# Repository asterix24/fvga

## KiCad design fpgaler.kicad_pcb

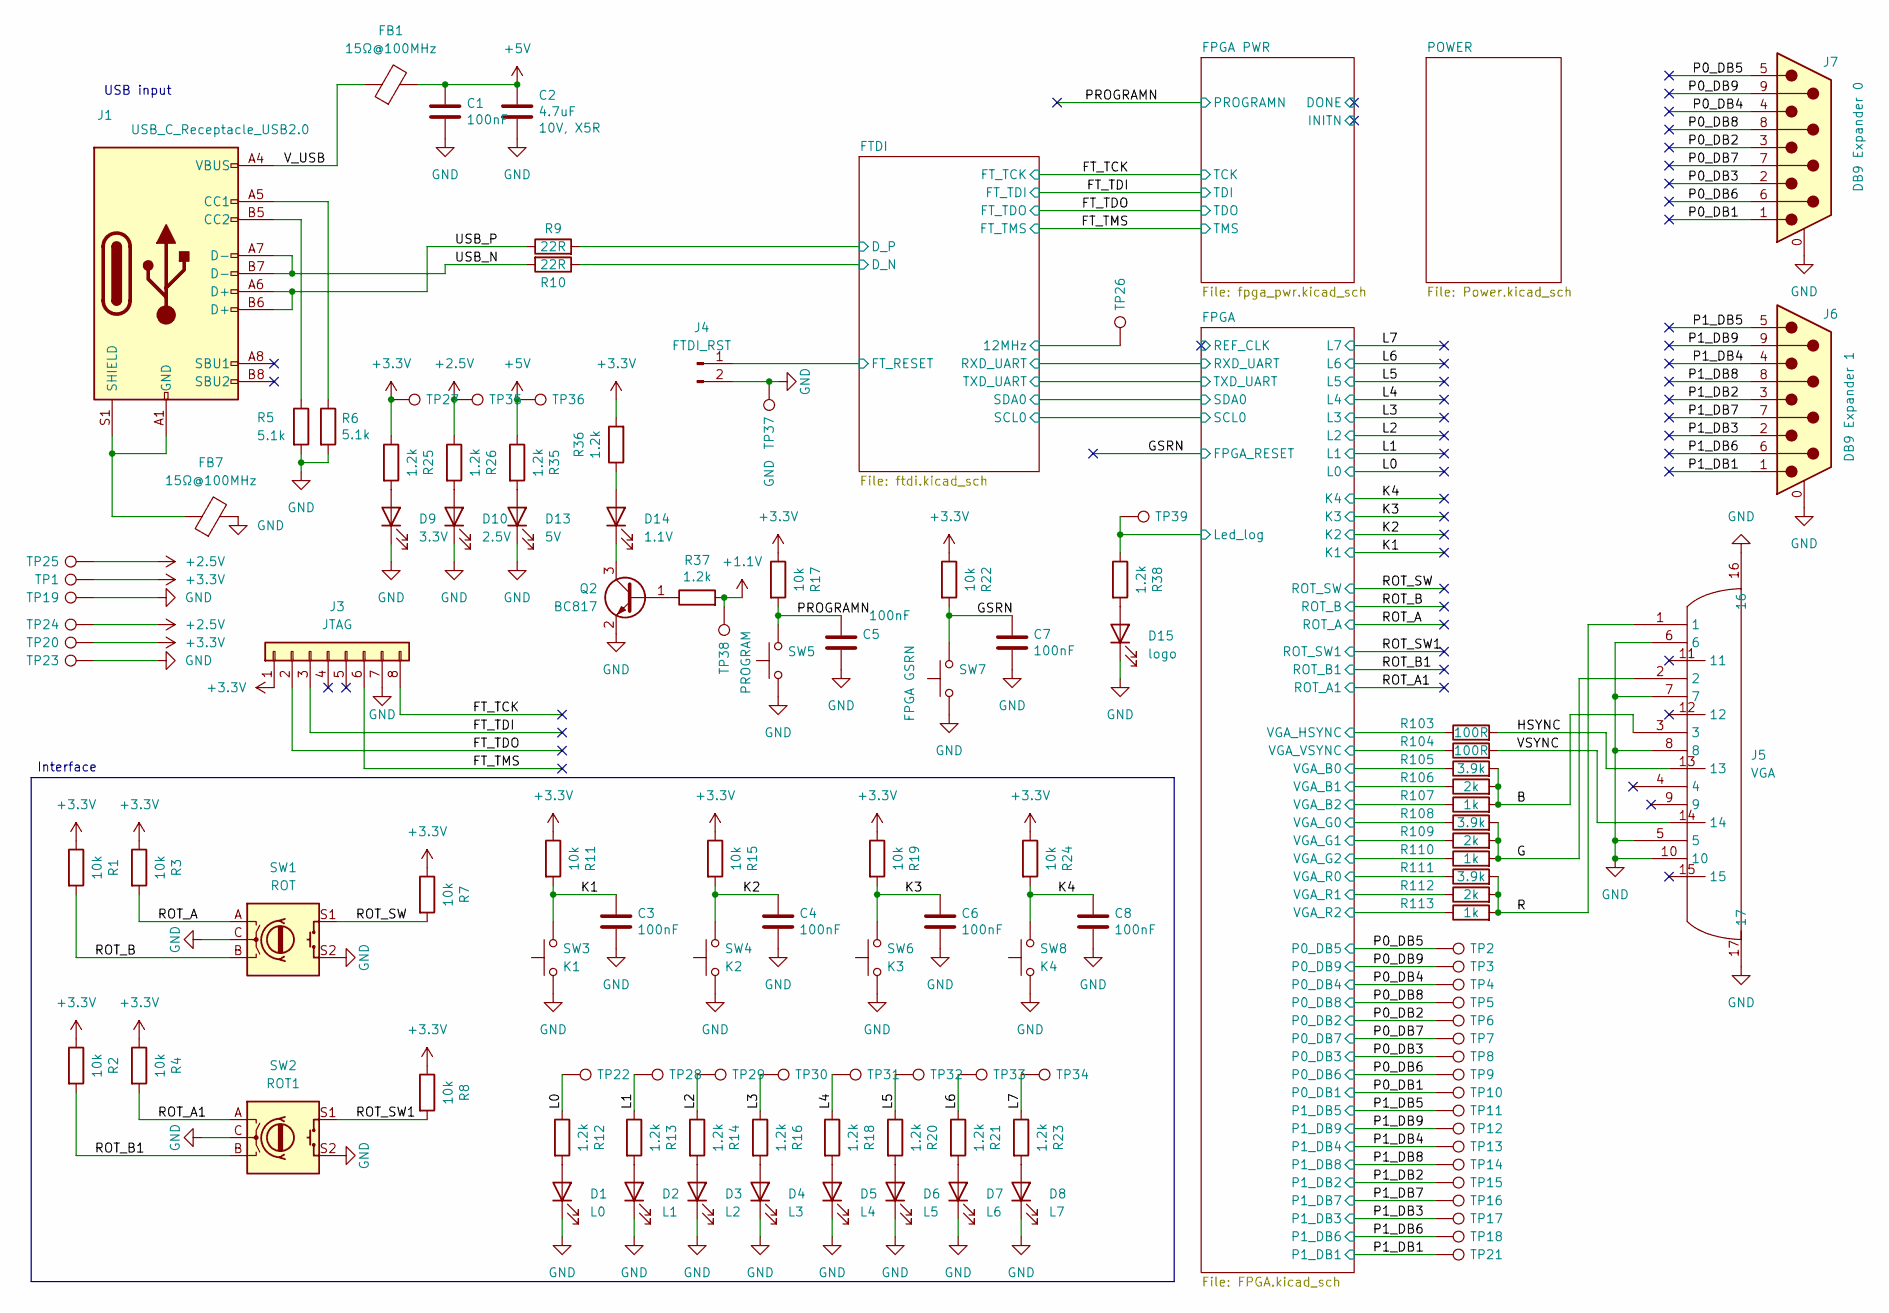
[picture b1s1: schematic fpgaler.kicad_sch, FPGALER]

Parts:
C1, C3, C4, C5, C6, C7, C8: 100nF; C_0603_1608Metric
C2: 4.7uF; C_0805_2012Metric
D1: L0; D_0603_1608Metric
D2: L1; D_0603_1608Metric
D3: L2; D_0603_1608Metric
D4: L3; D_0603_1608Metric
D5: L4; D_0603_1608Metric
D6: L5; D_0603_1608Metric
D7: L6; D_0603_1608Metric
D8: L7; D_0603_1608Metric
D9: 3.3V; D_0603_1608Metric
D10: 2.5V; D_0603_1608Metric
D13: 5V; D_0603_1608Metric
D14: 1.1V; D_0603_1608Metric
D15: logo; D_0603_1608Metric
FB1, FB7: 15Ω@100MHz; L_0603_1608Metric_Pad1.05x0.95mm_HandSolder
J1: USB_C_Receptacle_USB2.0; USB_C_Receptacle_HRO_TYPE-C-31-M-12
J3: JTAG; PinHeader_1x08_P2.54mm_Vertical
J4: FTDI_RST; PinHeader_1x02_P2.54mm_Vertical
J5: VGA; DSUB-TH_HYC06-HDR15B-060; Manufacturer Part HYC06-HDR15B-060; LCSC Part Name 高密度D-Sub 母 P数:15P
J6: DB9 Expander 1; DSUB-9_Pins_Horizontal_P2.77x2.84mm_EdgePinOffset4.94mm_Hou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
J7: DB9 Expander 0; DSUB-9_Pins_Horizontal_P2.77x2.84mm_EdgePinOffset4.94mm_Hou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
Q2: BC817; SOT-23
R1, R2, R3, R4, R7, R8, R11, R15, R17, R19, R22, R24: 10k; R_0603_1608Metric
R5, R6: 5.1k; R_0603_1608Metric
R9, R10: 22R; R_0402_1005Metric_Pad0.72x0.64mm_HandSolder
R12, R13, R14, R16, R18, R20, R21, R23, R25, R26, R35, R36, R37, R38: 1.2k; R_0603_1608Metric
R103, R104: 100R; R_0603_1608Metric
R105, R108, R111: 3.9k; R_0603_1608Metric
R106, R109, R112: 2k; R_0603_1608Metric
R107, R110, R113: 1k; R_0603_1608Metric
SW1: ROT; RotaryEncoder_Alps_EC11E-Switch_Vertical_H20mm_CircularMoun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
SW2: ROT1; RotaryEncoder_Alps_EC11E-Switch_Vertical_H20mm_CircularMoun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
SW3: K1; SW_PUSH_1P1T_6x3.5mm_H4.3_APEM_MJTP1243
SW4: K2; SW_PUSH_1P1T_6x3.5mm_H4.3_APEM_MJTP1243
SW5: PROGRAM; SW_PUSH_1P1T_6x3.5mm_H4.3_APEM_MJTP1243
SW6: K3; SW_PUSH_1P1T_6x3.5mm_H4.3_APEM_MJTP1243
SW7: FPGA GSRN; SW_PUSH_1P1T_6x3.5mm_H4.3_APEM_MJTP1243
SW8: K4; SW_PUSH_1P1T_6x3.5mm_H4.3_APEM_MJTP1243
TP1, TP2, TP3, TP4, TP5, TP6, TP7, TP8, TP9, TP10, TP11, TP12, TP13, TP14, TP15, TP16, TP17, TP18, TP19, TP20, TP21, TP22, TP23, TP24, TP25, TP26, TP28, TP29, TP30, TP31, TP32, TP33, TP34, TP39: TestPoint; TestPoint_THTPad_D1.5mm_Drill0.7mm
TP27: 3.3V; TestPoint_THTPad_D1.5mm_Drill0.7mm
TP35: 2.5V; TestPoint_THTPad_D1.5mm_Drill0.7mm
TP36, TP38: 5V; TestPoint_THTPad_D1.5mm_Drill0.7mm
TP37: GND; TestPoint_THTPad_D1.5mm_Drill0.7mm

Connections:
+1.1V: R37.2, TP38.1; also elsewhere on the board
+2.5V: R26.1, TP24.1, TP25.1, TP35.1; also elsewhere on the board
+3.3V: J3.1, R1.1, R2.1, R3.1, R4.1, R7.1, R8.1, R11.1, R15.1, R17.1, R19.1, R22.1, R24.1, R25.1, R36.2, TP1.1, TP20.1, TP27.1; also elsewhere on the board
+5V: C1.1, C2.1, FB1.2, R35.1, TP36.1; also elsewhere on the board
/B: J5.3, R105.2, R106.2, R107.2
/FPGA/Led_log: R38.1, TP39.1; also elsewhere on the board
/FPGA/VGA_B0: R105.1; also elsewhere on the board
/FPGA/VGA_B1: R106.1; also elsewhere on the board
/FPGA/VGA_B2: R107.1; also elsewhere on the board
/FPGA/VGA_G0: R108.1; also elsewhere on the board
/FPGA/VGA_G1: R109.1; also elsewhere on the board
/FPGA/VGA_G2: R110.1; also elsewhere on the board
/FPGA/VGA_HSYNC: R103.1; also elsewhere on the board
/FPGA/VGA_R0: R111.1; also elsewhere on the board
/FPGA/VGA_R1: R112.1; also elsewhere on the board
/FPGA/VGA_R2: R113.1; also elsewhere on the board
/FPGA/VGA_VSYNC: R104.1; also elsewhere on the board
/FTDI/12MHz: TP26.1; also elsewhere on the board
/FTDI/D_N: R10.1; also elsewhere on the board
/FTDI/D_P: R9.2; also elsewhere on the board
/FTDI/FT_RESET: J4.1; also elsewhere on the board
/FT_TCK: J3.8; also elsewhere on the board
/FT_TDI: J3.3; also elsewhere on the board
/FT_TDO: J3.2; also elsewhere on the board
/FT_TMS: J3.6; also elsewhere on the board
/G: J5.2, R108.2, R109.2, R110.2
/GSRN: C7.2, R22.2, SW7.2; also elsewhere on the board
/HSYNC: J5.13, R103.2
/K1: C3.2, R11.2, SW3.2; also elsewhere on the board
/K2: C4.2, R15.2, SW4.2; also elsewhere on the board
/K3: C6.2, R19.2, SW6.2; also elsewhere on the board
/K4: C8.2, R24.2, SW8.2; also elsewhere on the board
/L0: R12.1, TP22.1; also elsewhere on the board
/L1: R13.1, TP28.1; also elsewhere on the board
/L2: R14.1, TP29.1; also elsewhere on the board
/L3: R16.1, TP30.1; also elsewhere on the board
/L4: R18.1, TP31.1; also elsewhere on the board
/L5: R20.1, TP32.1; also elsewhere on the board
/L6: R21.1, TP33.1; also elsewhere on the board
/L7: R23.1, TP34.1; also elsewhere on the board
/P0_DB1: J7.1, TP10.1; also elsewhere on the board
/P0_DB2: J7.3, TP6.1; also elsewhere on the board
/P0_DB3: J7.2, TP8.1; also elsewhere on the board
/P0_DB4: J7.4, TP4.1; also elsewhere on the board
/P0_DB5: J7.5, TP2.1; also elsewhere on the board
/P0_DB6: J7.6, TP9.1; also elsewhere on the board
/P0_DB7: J7.7, TP7.1; also elsewhere on the board
/P0_DB8: J7.8, TP5.1; also elsewhere on the board
/P0_DB9: J7.9, TP3.1; also elsewhere on the board
/P1_DB1: J6.1, TP21.1; also elsewhere on the board
/P1_DB2: J6.3, TP15.1; also elsewhere on the board
/P1_DB3: J6.2, TP17.1; also elsewhere on the board
/P1_DB4: J6.4, TP13.1; also elsewhere on the board
/P1_DB5: J6.5, TP11.1; also elsewhere on the board
/P1_DB6: J6.6, TP18.1; also elsewhere on the board
/P1_DB7: J6.7, TP16.1; also elsewhere on the board
/P1_DB8: J6.8, TP14.1; also elsewhere on the board
/P1_DB9: J6.9, TP12.1; also elsewhere on the board
/PROGRAMN: C5.2, R17.2, SW5.2; also elsewhere on the board
/R: J5.1, R111.2, R112.2, R113.2
/ROT_A: R3.2, SW1.A; also elsewhere on the board
/ROT_A1: R4.2, SW2.A; also elsewhere on the board
/ROT_B: R1.2, SW1.B; also elsewhere on the board
/ROT_B1: R2.2, SW2.B; also elsewhere on the board
/ROT_SW: R7.2, SW1.S1; also elsewhere on the board
/ROT_SW1: R8.2, SW2.S1; also elsewhere on the board
/USB_N: J1.A7 (D-), J1.B7 (D-), R10.2
/USB_P: J1.A6 (D+), J1.B6 (D+), R9.1
/VSYNC: J5.14, R104.2
/V_USB: FB1.1, J1.A4 (VBUS), J1.A9 (VBUS), J1.B4 (VBUS), J1.B9 (VBUS)
GND: C1.2, C2.2, C3.1, C4.1, C5.1, C6.1, C7.1, C8.1, D1.1 (K), D2.1 (K), D3.1 (K), D4.1 (K), D5.1 (K), D6.1 (K), D7.1 (K), D8.1 (K), D9.1 (K), D10.1 (K), D13.1 (K), D15.1 (K), FB7.2, J3.7, J4.2, J5.5, J5.6, J5.7, J5.8, J5.10, J5.16, J5.17, J6.0 (PAD), J7.0 (PAD), Q2.2 (E), R5.2, R6.2, SW1.C, SW1.S2, SW2.C, SW2.S2, SW3.1, SW4.1, SW5.1, SW6.1, SW7.1, SW8.1, TP19.1, TP23.1, TP37.1; also elsewhere on the board
unnamed: D1.2 (A), R12.2
unnamed: D2.2 (A), R13.2
unnamed: D3.2 (A), R14.2
unnamed: D4.2 (A), R16.2
unnamed: D5.2 (A), R18.2
unnamed: D6.2 (A), R20.2
unnamed: D7.2 (A), R21.2
unnamed: D8.2 (A), R23.2
unnamed: D9.2 (A), R25.2
unnamed: D10.2 (A), R26.2
unnamed: D13.2 (A), R35.2
unnamed: D14.2 (A), R36.1
unnamed: D14.1 (K), Q2.3 (C)
unnamed: D15.2 (A), R38.2
unnamed: J1.A5 (CC1), R6.1
unnamed: J1.B5 (CC2), R5.1
unnamed: FB7.1, J1.A1 (GND), J1.A12 (GND), J1.B1 (GND), J1.B12 (GND), J1.S1 (SHIELD)
unnamed: Q2.1 (B), R37.1

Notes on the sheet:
Interface
USB input

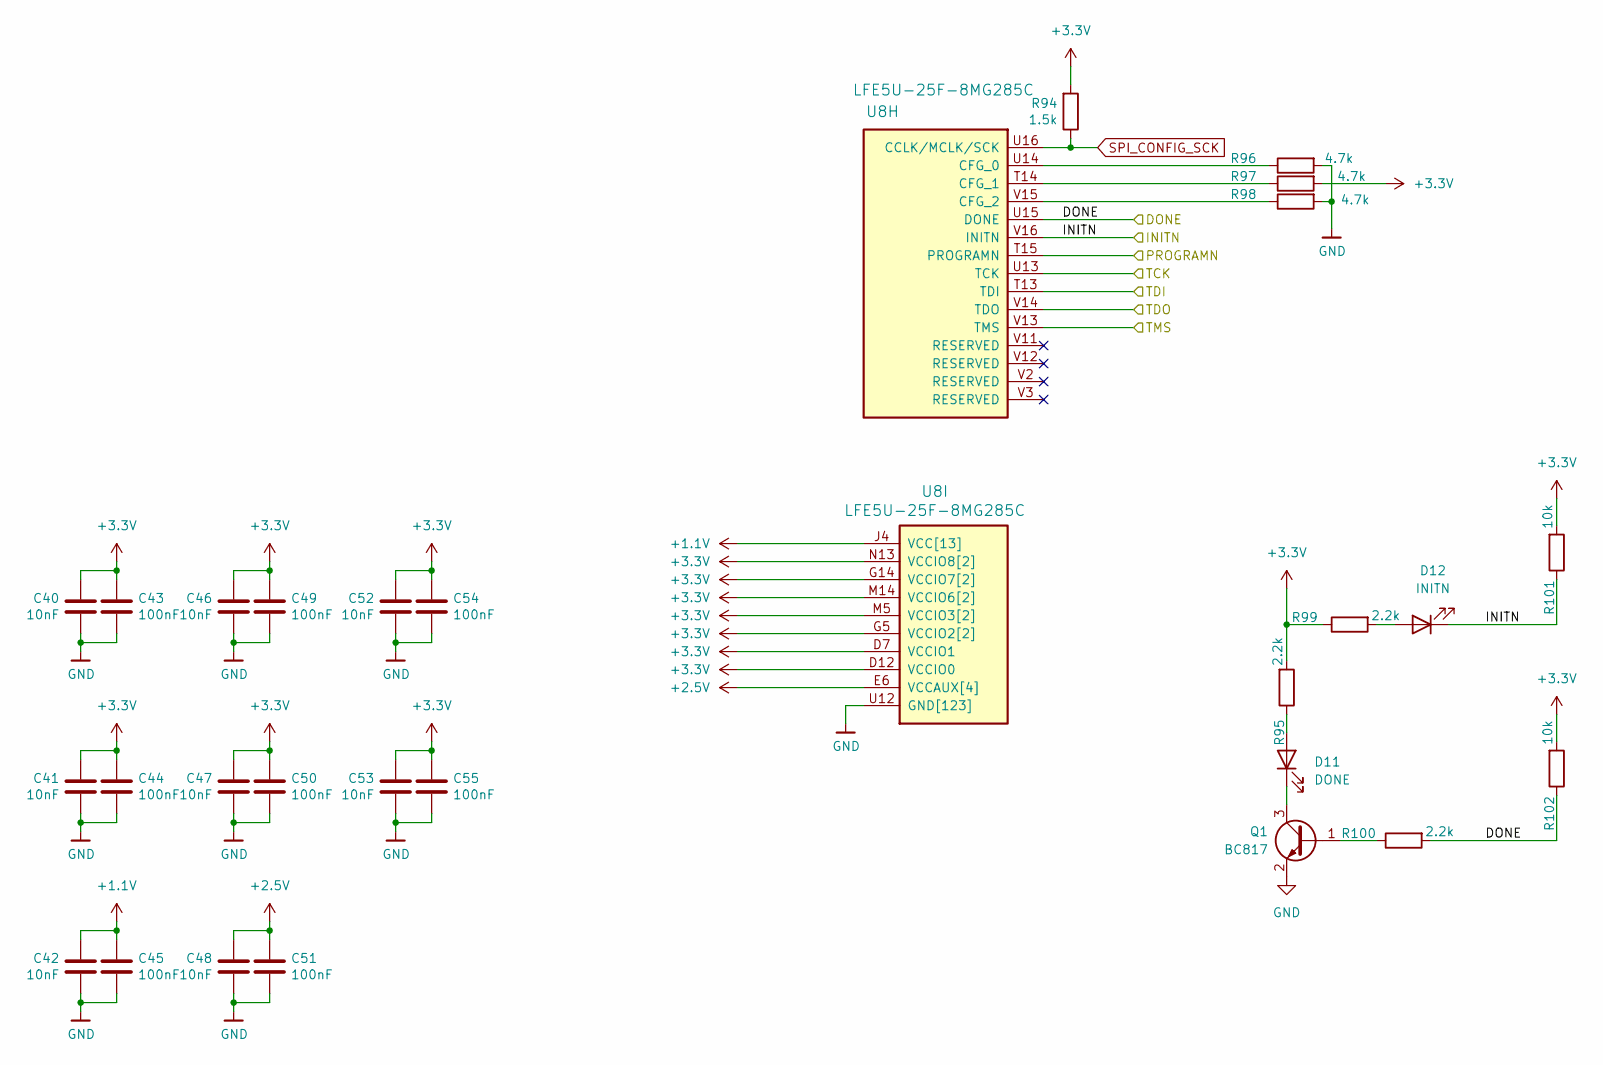
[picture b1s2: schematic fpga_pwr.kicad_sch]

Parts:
C40, C41, C42, C46, C47, C48, C52, C53: 10nF; C_0603_1608Metric
C43, C44, C45, C49, C50, C51, C54, C55: 100nF; C_0603_1608Metric
D11: DONE; D_0603_1608Metric
D12: INITN; D_0603_1608Metric
Q1: BC817; SOT-23
R94: 1.5k; R_0603_1608Metric; LCSC C22843
R95, R99: 2.2k; R_0603_1608Metric
R96, R97, R98: 4.7k; R_0603_1608Metric
R100: 2.2k; R_0603_1608Metric; LCSC C4190
R101, R102: 10k; R_0603_1608Metric
U8: LFE5U-25F-8MG285C; BGA-285; LCSC C5664013

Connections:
+1.1V: C42.1, C45.1, U8.D8 (VCC[13]), U8.D9 (VCC[13]), U8.D10 (VCC[13]), U8.D11 (VCC[13]), U8.J4 (VCC[13]), U8.J5 (VCC[13]), U8.J14 (VCC[13]), U8.J15 (VCC[13]), U8.M4 (VCC[13]), U8.M15 (VCC[13]), U8.P7 (VCC[13]), U8.P9 (VCC[13]), U8.P11 (VCC[13]); also elsewhere on the board
+2.5V: C48.1, C51.1, U8.E6 (VCCAUX[4]), U8.E13 (VCCAUX[4]), U8.N6 (VCCAUX[4]), U8.P13 (VCCAUX[4]); also elsewhere on the board
+3.3V: C40.1, C41.1, C43.1, C44.1, C46.1, C47.1, C49.1, C50.1, C52.1, C53.1, C54.1, C55.1, R94.2, R95.2, R97.2, R99.1, R101.2, R102.2, U8.D7 (VCCIO1), U8.D12 (VCCIO0), U8.G5 (VCCIO2[2]), U8.G14 (VCCIO7[2]), U8.H5 (VCCIO2[2]), U8.H14 (VCCIO7[2]), U8.M5 (VCCIO3[2]), U8.M14 (VCCIO6[2]), U8.N5 (VCCIO3[2]), U8.N13 (VCCIO8[2]), U8.N14 (VCCIO6[2]), U8.P14 (VCCIO8[2]); also elsewhere on the board
/FPGA PWR/DONE: R100.2, R102.1, U8.U15 (DONE)
/FPGA PWR/INITN: D12.1 (K), R101.1, U8.V16 (INITN)
/FT_TCK: U8.U13 (TCK); also elsewhere on the board
/FT_TDI: U8.T13 (TDI); also elsewhere on the board
/FT_TDO: U8.V14 (TDO); also elsewhere on the board
/FT_TMS: U8.V13 (TMS); also elsewhere on the board
/PROGRAMN: U8.T15 (PROGRAMN); also elsewhere on the board
GND: C40.2, C41.2, C42.2, C43.2, C44.2, C45.2, C46.2, C47.2, C48.2, C49.2, C50.2, C51.2, C52.2, C53.2, C54.2, C55.2, Q1.2 (E), R96.2, R98.2, U8.B3 (GND[123]), U8.B16 (GND[123]), U8.E5 (GND[123]), U8.E7 (GND[123]), U8.E8 (GND[123]), U8.E9 (GND[123]), U8.E10 (GND[123]), U8.E11 (GND[123]), U8.E12 (GND[123]), U8.E14 (GND[123]), U8.F5 (GND[123]), U8.F6 (GND[123]), U8.F7 (GND[123]), U8.F8 (GND[123]), U8.F9 (GND[123]), U8.F10 (GND[123]), U8.F11 (GND[123]), U8.F12 (GND[123]), U8.F13 (GND[123]), U8.F14 (GND[123]), U8.G2 (GND[123]), U8.G6 (GND[123]), U8.G7 (GND[123]), U8.G8 (GND[123]), U8.G9 (GND[123]), U8.G10 (GND[123]), U8.G11 (GND[123]), U8.G12 (GND[123]), U8.G13 (GND[123]), U8.G17 (GND[123]), U8.H6 (GND[123]), U8.H7 (GND[123]), U8.H8 (GND[123]), U8.H9 (GND[123]), U8.H10 (GND[123]), U8.H11 (GND[123]), U8.H12 (GND[123]), U8.H13 (GND[123]), U8.J6 (GND[123]), U8.J7 (GND[123]), U8.J8 (GND[123]), U8.J9 (GND[123]), U8.J10 (GND[123]), U8.J11 (GND[123]), U8.J12 (GND[123]), U8.J13 (GND[123]), U8.K5 (GND[123]), U8.K6 (GND[123]), U8.K7 (GND[123]), U8.K8 (GND[123]), U8.K9 (GND[123]), U8.K10 (GND[123]), U8.K11 (GND[123]), U8.K12 (GND[123]), U8.K13 (GND[123]), U8.K14 (GND[123]), U8.L2 (GND[123]), U8.L5 (GND[123]), U8.L6 (GND[123]), U8.L7 (GND[123]), U8.L8 (GND[123]), U8.L9 (GND[123]), U8.L10 (GND[123]), U8.L11 (GND[123]), U8.L12 (GND[123]), U8.L13 (GND[123]), U8.L14 (GND[123]), U8.L17 (GND[123]), U8.M6 (GND[123]), U8.M7 (GND[123]), U8.M8 (GND[123]), U8.M9 (GND[123]), U8.M10 (GND[123]), U8.M11 (GND[123]), U8.M12 (GND[123]), U8.M13 (GND[123]), U8.N7 (GND[123]), U8.N8 (GND[123]), U8.N9 (GND[123]), U8.N10 (GND[123]), U8.N11 (GND[123]), U8.N12 (GND[123]), U8.P5 (GND[123]), U8.P6 (GND[123]), U8.P8 (GND[123]), U8.P10 (GND[123]), U8.P12 (GND[123]), U8.R1 (GND[123]), U8.R2 (GND[123]), U8.R3 (GND[123]), U8.R10 (GND[123]), U8.T1 (GND[123]), U8.T2 (GND[123]), U8.T3 (GND[123]), U8.T4 (GND[123]), U8.T5 (GND[123]), U8.T6 (GND[123]), U8.T7 (GND[123]), U8.T8 (GND[123]), U8.T9 (GND[123]), U8.T10 (GND[123]), U8.T11 (GND[123]), U8.T12 (GND[123]), U8.T16 (GND[123]), U8.U1 (GND[123]), U8.U2 (GND[123]), U8.U3 (GND[123]), U8.U4 (GND[123]), U8.U5 (GND[123]), U8.U6 (GND[123]), U8.U7 (GND[123]), U8.U8 (GND[123]), U8.U9 (GND[123]), U8.U10 (GND[123]), U8.U11 (GND[123]), U8.U12 (GND[123]), U8.V4 (GND[123]), U8.V5 (GND[123]), U8.V6 (GND[123]), U8.V7 (GND[123]), U8.V8 (GND[123]), U8.V9 (GND[123]), U8.V10 (GND[123]); also elsewhere on the board
unnamed: D11.2 (A), R95.1
unnamed: D11.1 (K), Q1.3 (C)
unnamed: D12.2 (A), R99.2
unnamed: Q1.1 (B), R100.1
unnamed: R96.1, U8.U14 (CFG_0)
unnamed: R97.1, U8.T14 (CFG_1)
unnamed: R98.1, U8.V15 (CFG_2)
SPI_CONFIG_SCK: R94.1, U8.U16 (CCLK/MCLK/SCK); also elsewhere on the board

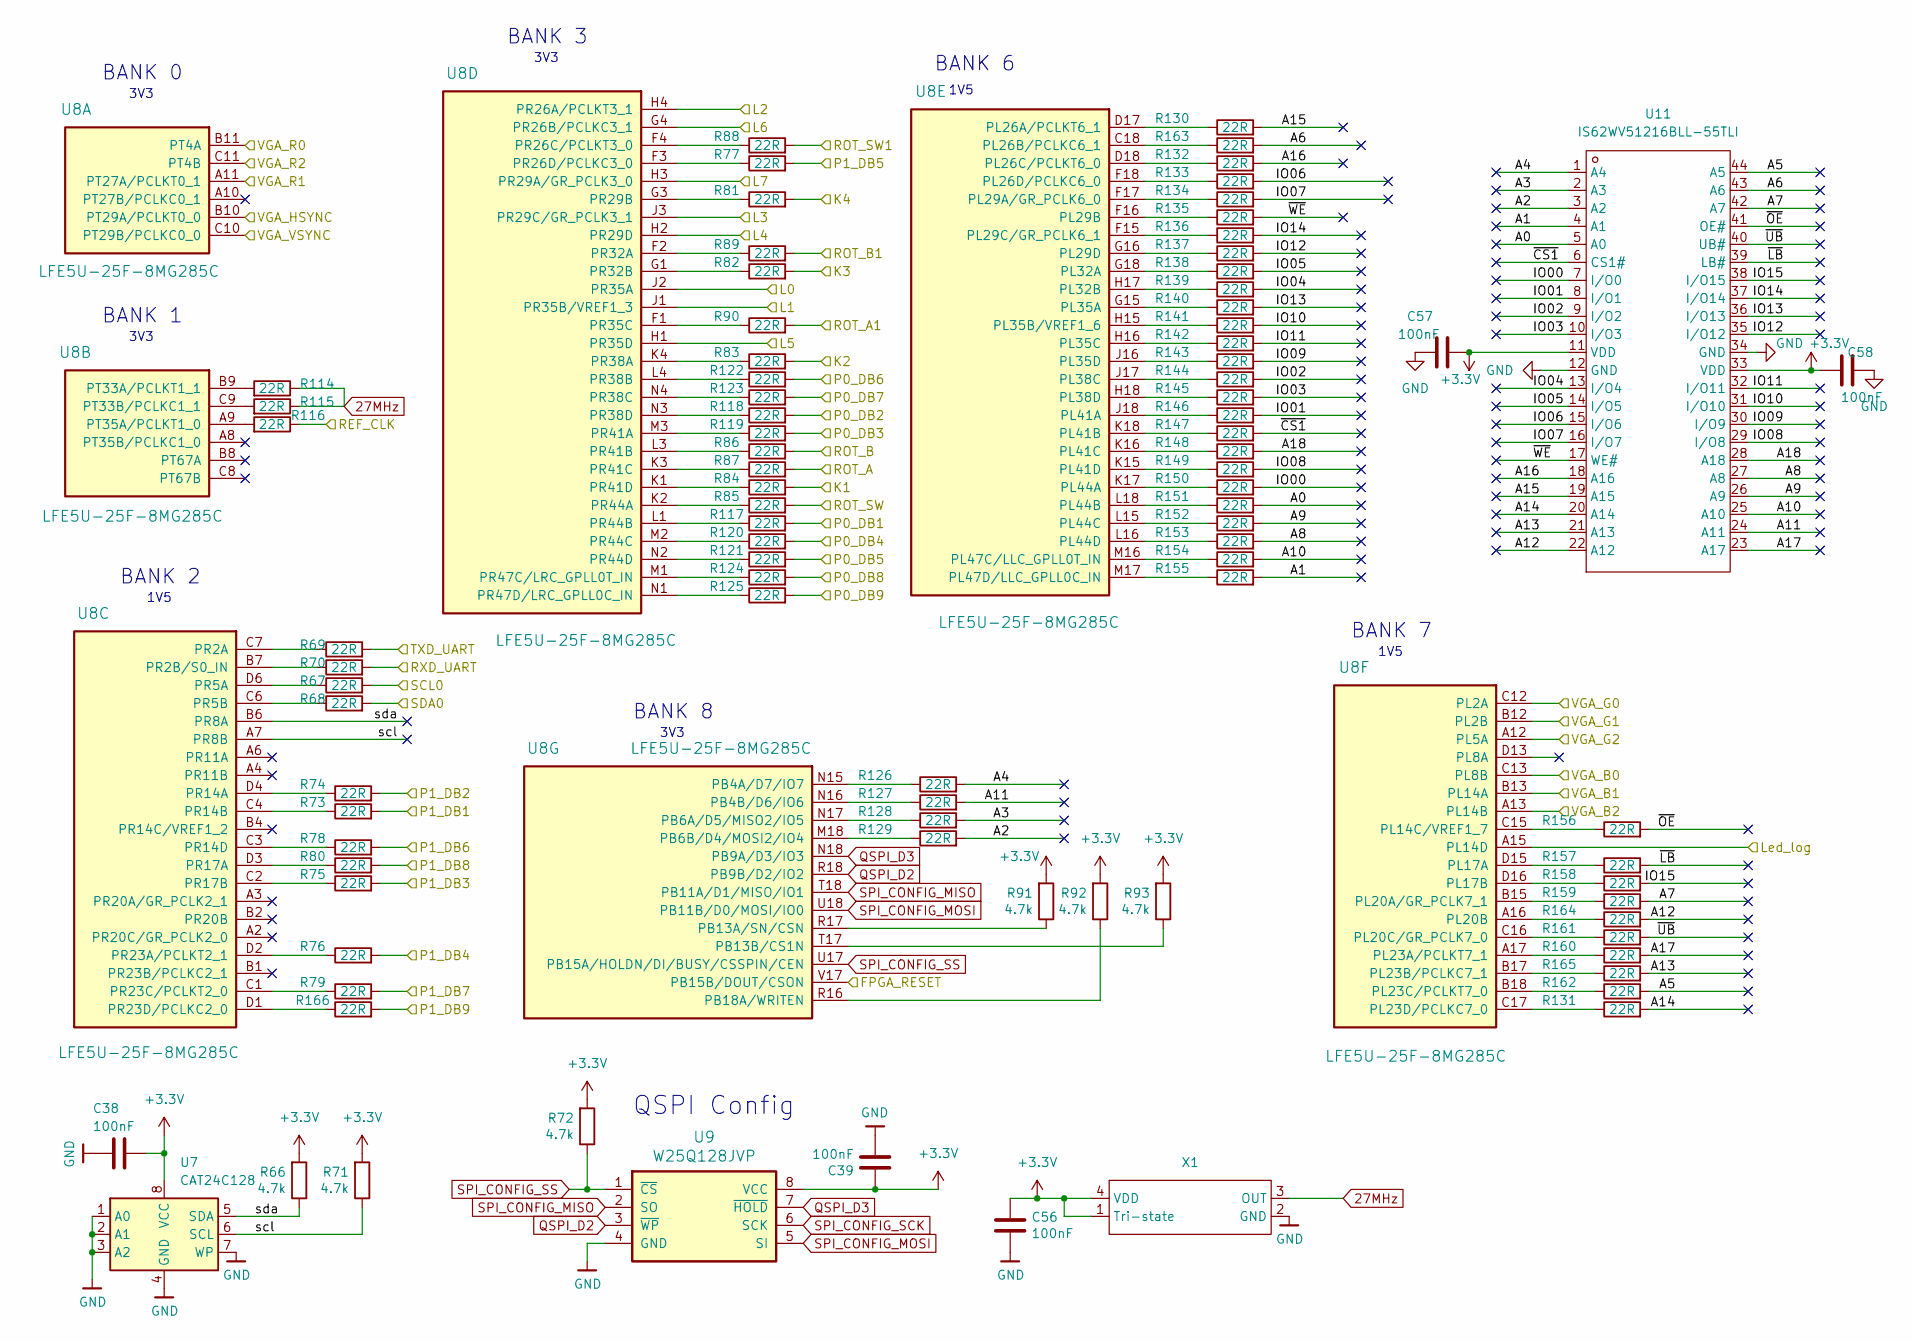
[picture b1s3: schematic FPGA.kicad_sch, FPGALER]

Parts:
C38, C39, C56, C57, C58: 100nF; C_0603_1608Metric
R66, R71, R72, R91, R92, R93: 4.7k; R_0603_1608Metric
R67, R68, R69, R70, R73, R74, R75, R76, R77, R78, R79, R80, R81, R82, R83, R84, R85, R86, R87, R88, R89, R90, R114, R115, R116, R117, R118, R119, R120, R121, R122, R123, R124, R125, R126, R127, R128, R129, R130, R131, R132, R133, R134, R135, R136, R137, R138, R139, R140, R141, R142, R143, R144, R145, R146, R147, R148, R149, R150, R151, R152, R153, R154, R155, R156, R157, R158, R159, R160, R161, R162, R163, R164, R165, R166: 22R; R_0402_1005Metric_Pad0.72x0.64mm_HandSolder
U7: CAT24C128; SOIC-8_3.9x4.9mm_P1.27mm
U8: LFE5U-25F-8MG285C; BGA-285; LCSC C5664013
U9: W25Q128JVP; WSON-8-1EP_6x5mm_P1.27mm_EP3.4x4mm; LCSC C190862
U11: IS62WV51216BLL-55TLI; TSOP-44_L18.4-W10.2-P0.80-LS11.8-BL; Manufacturer Part IS62WV51216BLL-55TLI; LCSC Part Name 512K X 16 低电压超低功耗CMOS静态RAM
X1: 27MHz; OSC-SMD_4P-L3.2-W2.5-BL; Manufacturer Part OT2EL4C4JI-111OLP-27M; LCSC Part Name YSO110TR 27MHZ 1.8V-3.3V ±10PPM -40~85°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

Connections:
27MHz: R114.1, R115.1, X1.3 (OUT)
+3.3V: C38.1, C39.1, C56.1, C57.1, C58.1, R66.2, R71.2, R72.2, R91.2, R92.2, R93.2, U7.8 (VCC), U9.8 (VCC), U11.11 (VDD), U11.33 (VDD), X1.1 (Tri-state), X1.4 (VDD); also elsewhere on the board
/FPGA/A0: R151.2, U11.5 (A0)
/FPGA/A1: R155.2, U11.4 (A1)
/FPGA/A2: R129.2, U11.3 (A2)
/FPGA/A3: R128.2, U11.2 (A3)
/FPGA/A4: R126.2, U11.1 (A4)
/FPGA/A5: R162.2, U11.44 (A5)
/FPGA/A6: R163.2, U11.43 (A6)
/FPGA/A7: R159.2, U11.42 (A7)
/FPGA/A8: R153.2, U11.27 (A8)
/FPGA/A9: R152.2, U11.26 (A9)
/FPGA/A10: R154.2, U11.25 (A10)
/FPGA/A11: R127.2, U11.24 (A11)
/FPGA/A12: R164.2, U11.22 (A12)
/FPGA/A13: R165.2, U11.21 (A13)
/FPGA/A14: R131.2, U11.20 (A14)
/FPGA/A15: R130.2, U11.19 (A15)
/FPGA/A16: R132.2, U11.18 (A16)
/FPGA/A17: R160.2, U11.23 (A17)
/FPGA/A18: R148.2, U11.28 (A18)
/FPGA/IO00: R150.2, U11.7 (I/O0)
/FPGA/IO01: R146.2, U11.8 (I/O1)
/FPGA/IO02: R144.2, U11.9 (I/O2)
/FPGA/IO03: R145.2, U11.10 (I/O3)
/FPGA/IO04: R139.2, U11.13 (I/O4)
/FPGA/IO05: R138.2, U11.14 (I/O5)
/FPGA/IO06: R133.2, U11.15 (I/O6)
/FPGA/IO07: R134.2, U11.16 (I/O7)
/FPGA/IO08: R149.2, U11.29 (I/O8)
/FPGA/IO09: R143.2, U11.30 (I/O9)
/FPGA/IO10: R141.2, U11.31 (I/O10)
/FPGA/IO11: R142.2, U11.32 (I/O11)
/FPGA/IO12: R137.2, U11.35 (I/O12)
/FPGA/IO13: R140.2, U11.36 (I/O13)
/FPGA/IO14: R136.2, U11.37 (I/O14)
/FPGA/IO15: R158.2, U11.38 (I/O15)
/FPGA/Led_log: U8.A15 (PL14D); also elsewhere on the board
/FPGA/REF_CLK: R116.1
/FPGA/RXD_UART: R70.2; also elsewhere on the board
/FPGA/SCL0: R67.2; also elsewhere on the board
/FPGA/SDA0: R68.2; also elsewhere on the board
/FPGA/TXD_UART: R69.2; also elsewhere on the board
/FPGA/VGA_B0: U8.C13 (PL8B); also elsewhere on the board
/FPGA/VGA_B1: U8.B13 (PL14A); also elsewhere on the board
/FPGA/VGA_B2: U8.A13 (PL14B); also elsewhere on the board
/FPGA/VGA_G0: U8.C12 (PL2A); also elsewhere on the board
/FPGA/VGA_G1: U8.B12 (PL2B); also elsewhere on the board
/FPGA/VGA_G2: U8.A12 (PL5A); also elsewhere on the board
/FPGA/VGA_HSYNC: U8.B10 (PT29A/PCLKT0_0); also elsewhere on the board
/FPGA/VGA_R0: U8.B11 (PT4A); also elsewhere on the board
/FPGA/VGA_R1: U8.A11 (PT27A/PCLKT0_1); also elsewhere on the board
/FPGA/VGA_R2: U8.C11 (PT4B); also elsewhere on the board
/FPGA/VGA_VSYNC: U8.C10 (PT29B/PCLKC0_0); also elsewhere on the board
/FPGA/scl: R71.1, U7.6 (SCL), U8.A7 (PR8B)
/FPGA/sda: R66.1, U7.5 (SDA), U8.B6 (PR8A)
/FPGA/~CS1: R147.2, U11.6 (CS1#)
/FPGA/~LB: R157.2, U11.39 (LB#)
/FPGA/~OE: R156.2, U11.41 (OE#)
/FPGA/~UB: R161.2, U11.40 (UB#)
/FPGA/~WE: R135.2, U11.17 (WE#)
/GSRN: U8.V17 (PB15B/DOUT/CSON); also elsewhere on the board
/K1: R84.2; also elsewhere on the board
/K2: R83.2; also elsewhere on the board
/K3: R82.2; also elsewhere on the board
/K4: R81.2; also elsewhere on the board
/L0: U8.J2 (PR35A); also elsewhere on the board
/L1: U8.J1 (PR35B/VREF1_3); also elsewhere on the board
/L2: U8.H4 (PR26A/PCLKT3_1); also elsewhere on the board
/L3: U8.J3 (PR29C/GR_PCLK3_1); also elsewhere on the board
/L4: U8.H2 (PR29D); also elsewhere on the board
/L5: U8.H1 (PR35D); also elsewhere on the board
/L6: U8.G4 (PR26B/PCLKC3_1); also elsewhere on the board
/L7: U8.H3 (PR29A/GR_PCLK3_0); also elsewhere on the board
/P0_DB1: R117.2; also elsewhere on the board
/P0_DB2: R118.2; also elsewhere on the board
/P0_DB3: R119.2; also elsewhere on the board
/P0_DB4: R120.2; also elsewhere on the board
/P0_DB5: R121.2; also elsewhere on the board
/P0_DB6: R122.2; also elsewhere on the board
/P0_DB7: R123.2; also elsewhere on the board
/P0_DB8: R124.2; also elsewhere on the board
/P0_DB9: R125.2; also elsewhere on the board
/P1_DB1: R73.2; also elsewhere on the board
/P1_DB2: R74.2; also elsewhere on the board
/P1_DB3: R75.2; also elsewhere on the board
/P1_DB4: R76.2; also elsewhere on the board
/P1_DB5: R77.2; also elsewhere on the board
/P1_DB6: R78.2; also elsewhere on the board
/P1_DB7: R79.2; also elsewhere on the board
/P1_DB8: R80.2; also elsewhere on the board
/P1_DB9: R166.2; also elsewhere on the board
/ROT_A: R87.2; also elsewhere on the board
/ROT_A1: R90.2; also elsewhere on the board
/ROT_B: R86.2; also elsewhere on the board
/ROT_B1: R89.2; also elsewhere on the board
/ROT_SW: R85.2; also elsewhere on the board
/ROT_SW1: R88.2; also elsewhere on the board
GND: C38.2, C39.2, C56.2, C57.2, C58.2, U7.1 (A0), U7.2 (A1), U7.3 (A2), U7.4 (GND), U7.7 (WP), U9.4 (GND), U11.12 (GND), U11.34 (GND), X1.2 (GND); also elsewhere on the board
unnamed: R114.2, U8.B9 (PT33A/PCLKT1_1)
unnamed: R115.2, U8.C9 (PT33B/PCLKC1_1)
unnamed: R116.2, U8.A9 (PT35A/PCLKT1_0)
unnamed: R69.1, U8.C7 (PR2A)
unnamed: R70.1, U8.B7 (PR2B/S0_IN)
unnamed: R67.1, U8.D6 (PR5A)
unnamed: R68.1, U8.C6 (PR5B)
unnamed: R74.1, U8.D4 (PR14A)
unnamed: R73.1, U8.C4 (PR14B)
unnamed: R78.1, U8.C3 (PR14D)
unnamed: R80.1, U8.D3 (PR17A)
unnamed: R75.1, U8.C2 (PR17B)
unnamed: R76.1, U8.D2 (PR23A/PCLKT2_1)
unnamed: R79.1, U8.C1 (PR23C/PCLKT2_0)
unnamed: R166.1, U8.D1 (PR23D/PCLKC2_0)
unnamed: R88.1, U8.F4 (PR26C/PCLKT3_0)
unnamed: R77.1, U8.F3 (PR26D/PCLKC3_0)
unnamed: R81.1, U8.G3 (PR29B)
unnamed: R89.1, U8.F2 (PR32A)
unnamed: R82.1, U8.G1 (PR32B)
unnamed: R90.1, U8.F1 (PR35C)
unnamed: R83.1, U8.K4 (PR38A)
unnamed: R122.1, U8.L4 (PR38B)
unnamed: R123.1, U8.N4 (PR38C)
unnamed: R118.1, U8.N3 (PR38D)
unnamed: R119.1, U8.M3 (PR41A)
unnamed: R86.1, U8.L3 (PR41B)
unnamed: R87.1, U8.K3 (PR41C)
unnamed: R84.1, U8.K1 (PR41D)
unnamed: R85.1, U8.K2 (PR44A)
unnamed: R117.1, U8.L1 (PR44B)
unnamed: R120.1, U8.M2 (PR44C)
unnamed: R121.1, U8.N2 (PR44D)
unnamed: R124.1, U8.M1 (PR47C/LRC_GPLL0T_IN)
unnamed: R125.1, U8.N1 (PR47D/LRC_GPLL0C_IN)
unnamed: R130.1, U8.D17 (PL26A/PCLKT6_1)
unnamed: R163.1, U8.C18 (PL26B/PCLKC6_1)
unnamed: R132.1, U8.D18 (PL26C/PCLKT6_0)
unnamed: R133.1, U8.F18 (PL26D/PCLKC6_0)
unnamed: R134.1, U8.F17 (PL29A/GR_PCLK6_0)
unnamed: R135.1, U8.F16 (PL29B)
unnamed: R136.1, U8.F15 (PL29C/GR_PCLK6_1)
unnamed: R137.1, U8.G16 (PL29D)
unnamed: R138.1, U8.G18 (PL32A)
unnamed: R139.1, U8.H17 (PL32B)
unnamed: R140.1, U8.G15 (PL35A)
unnamed: R141.1, U8.H15 (PL35B/VREF1_6)
unnamed: R142.1, U8.H16 (PL35C)
unnamed: R143.1, U8.J16 (PL35D)
unnamed: R144.1, U8.J17 (PL38C)
unnamed: R145.1, U8.H18 (PL38D)
unnamed: R146.1, U8.J18 (PL41A)
unnamed: R147.1, U8.K18 (PL41B)
unnamed: R148.1, U8.K16 (PL41C)
unnamed: R149.1, U8.K15 (PL41D)
unnamed: R150.1, U8.K17 (PL44A)
unnamed: R151.1, U8.L18 (PL44B)
unnamed: R152.1, U8.L15 (PL44C)
unnamed: R153.1, U8.L16 (PL44D)
unnamed: R154.1, U8.M16 (PL47C/LLC_GPLL0T_IN)
unnamed: R155.1, U8.M17 (PL47D/LLC_GPLL0C_IN)
unnamed: R156.1, U8.C15 (PL14C/VREF1_7)
unnamed: R157.1, U8.D15 (PL17A)
unnamed: R158.1, U8.D16 (PL17B)
unnamed: R159.1, U8.B15 (PL20A/GR_PCLK7_1)
unnamed: R164.1, U8.A16 (PL20B)
unnamed: R161.1, U8.C16 (PL20C/GR_PCLK7_0)
unnamed: R160.1, U8.A17 (PL23A/PCLKT7_1)
unnamed: R165.1, U8.B17 (PL23B/PCLKC7_1)
unnamed: R162.1, U8.B18 (PL23C/PCLKT7_0)
unnamed: R131.1, U8.C17 (PL23D/PCLKC7_0)
unnamed: R126.1, U8.N15 (PB4A/D7/IO7)
unnamed: R127.1, U8.N16 (PB4B/D6/IO6)
unnamed: R128.1, U8.N17 (PB6A/D5/MISO2/IO5)
unnamed: R129.1, U8.M18 (PB6B/D4/MOSI2/IO4)
unnamed: R91.1, U8.R17 (PB13A/SN/CSN)
unnamed: R93.1, U8.T17 (PB13B/CS1N)
unnamed: R92.1, U8.R16 (PB18A/WRITEN)
QSPI_D2: U8.R18 (PB9B/D2/IO2), U9.3 (~WP)
QSPI_D3: U8.N18 (PB9A/D3/IO3), U9.7 (~HOLD)
SPI_CONFIG_MISO: U8.T18 (PB11A/D1/MISO/IO1), U9.2 (SO)
SPI_CONFIG_MOSI: U8.U18 (PB11B/D0/MOSI/IO0), U9.5 (SI)
SPI_CONFIG_SCK: U9.6 (SCK); also elsewhere on the board
SPI_CONFIG_SS: R72.1, U8.U17 (PB15A/HOLDN/DI/BUSY/CSSPIN/CEN), U9.1 (~CS)

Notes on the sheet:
BANK 3
1V5
BANK 0
3V3
BANK 2
3V3
BANK 1
QSPI Config
BANK 8
1V5
BANK 6
BANK 7

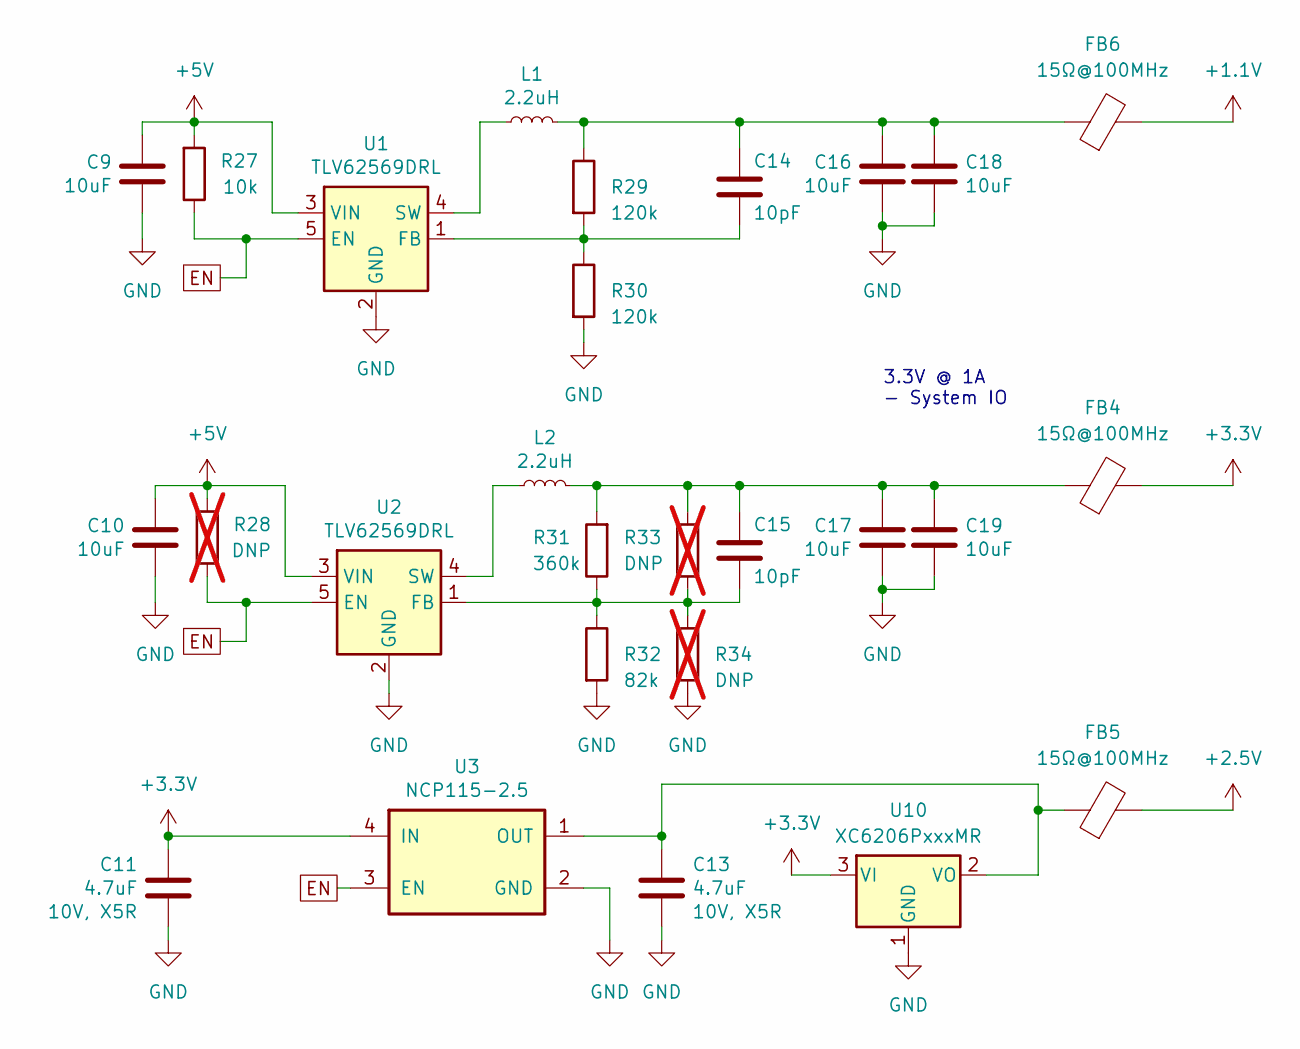
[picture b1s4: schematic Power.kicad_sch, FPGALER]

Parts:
C9, C10, C16, C17, C18, C19: 10uF; C_1206_3216Metric
C11, C13: 4.7uF; C_0805_2012Metric
C14, C15: 10pF; C_0603_1608Metric
FB4, FB5, FB6: 15Ω@100MHz; L_0603_1608Metric_Pad1.05x0.95mm_HandSolder
L1: 2.2uH; L_0805_2012Metric; LCSC C216156
L2: 2.2uH; L_0805_2012Metric
R27: 10k; R_0603_1608Metric
R28, R33, R34: DNP; R_0603_1608Metric; not fitted
R29: 120k; R_0603_1608Metric
R30: 120k; R_0603_1608Metric; LCSC C25808
R31: 360k; R_0603_1608Metric; LCSC C23146
R32: 82k; R_0603_1608Metric; LCSC C23254
U1, U2: TLV62569DRL; SOT-563
U3: NCP115-2.5; Texas_X2SON-4_1x1mm_P0.65mm; LCSC C603508
U10: XC6206PxxxMR; SOT-23-3; LCSC C15906

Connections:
+1.1V: FB6.2; also elsewhere on the board
+2.5V: FB5.2; also elsewhere on the board
+3.3V: C11.1, FB4.2, U3.4 (IN), U10.3 (VI); also elsewhere on the board
+5V: C9.2, C10.2, R27.2, R28.2, U1.3 (VIN), U2.3 (VIN); also elsewhere on the board
EN: R27.1, R28.1, U1.5 (EN), U2.5 (EN), U3.3 (EN)
GND: C9.1, C10.1, C11.2, C13.2, C16.1, C17.1, C18.1, C19.1, R30.2, R32.2, R34.2, U1.2 (GND), U2.2 (GND), U3.2 (GND), U10.1 (GND); also elsewhere on the board
unnamed: C14.2, C16.2, C18.2, FB6.1, L1.2, R29.1
unnamed: C15.2, C17.2, C19.2, FB4.1, L2.2, R31.2, R33.2
unnamed: C14.1, R29.2, R30.1, U1.1 (FB)
unnamed: L1.1, U1.4 (SW)
unnamed: C15.1, R31.1, R32.1, R33.1, R34.1, U2.1 (FB)
unnamed: L2.1, U2.4 (SW)
unnamed: C13.1, FB5.1, U3.1 (OUT), U10.2 (VO)

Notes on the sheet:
3.3V @ 1A - System IO
